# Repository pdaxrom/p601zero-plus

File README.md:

## Pyldin-601 compatible retrocomputer.

[History](docs/HISTORY.md)

### Overview hardware version 2.0:

 Function | Description 
----|----
CPU | [System 11 - VHDL 68HC11](http://members.optusnet.com.au/jekent/system11/)
FPGA| [Lattice MachXO2-4000HC module](http://www.stepfpga.com)
RAM | Builtin FPGA 4KB and/or external static serial ram 2x128KB
ROM | Builtin FPGA BOOTROM 2KB
Keyboard | PS/2
Serial port | 1 serial port and 1 UART (rx/tx only)
Parallel port | 2x8bit
Video | TV (color, 8bit DAC)
Audio | YMZ284-D (mono)
Storage | MMC/SD
Other | Onboard SPI, 4 CS ports and Reset.

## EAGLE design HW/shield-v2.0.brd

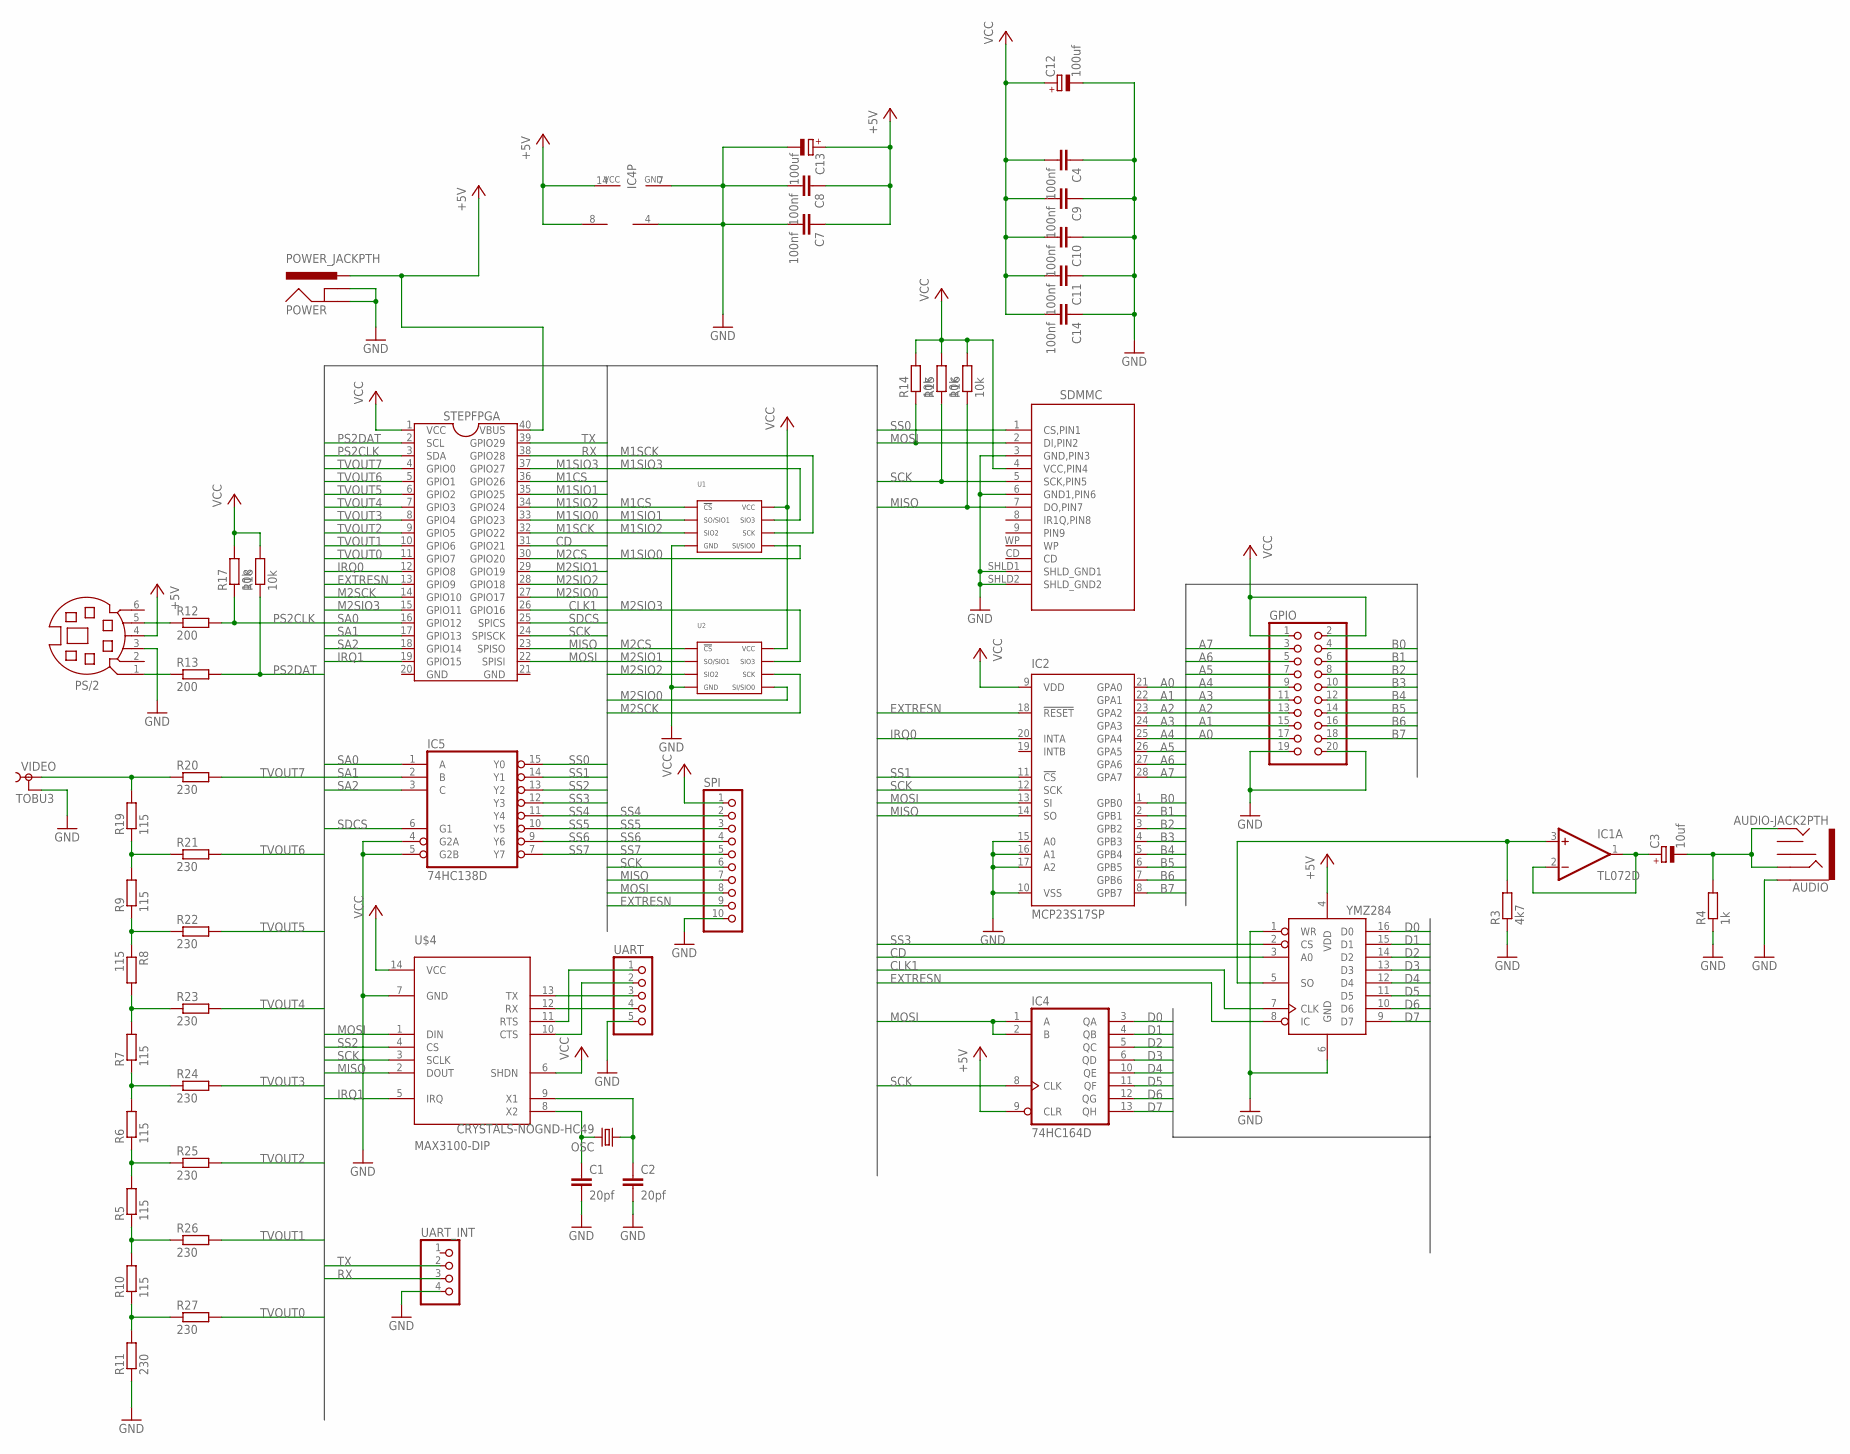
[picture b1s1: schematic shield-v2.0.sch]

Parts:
AUDIO: AUDIO-JACK2PTH; AUDIO-JACK
C1, C2: 20pf; 1206
C3: 10uf; E5-5
C4, C7, C8, C9, C10, C11, C14: 100nf; 1206
C12, C13: 100uf; E5-5
GPIO: PINHD-2X10; 2X10
IC1: TL072D; SO08
IC2: MCP23S17SP; DIL28-3
IC3: YMZ284; DIL16
IC4: 74HC164D; SO14
IC5: 74HC138D; SO16
OSC: CRYSTALS-NOGND-HC49; HC49
POWER: POWER_JACKPTH; POWER_JACK_PTH
PS/2: MD06SS; MDIN06SS
R3: 4k7; R1206
R4: 1k; R1206
R5, R6, R7, R8, R9, R10, R19: 115; R1206
R11, R20, R21, R22, R23, R24, R25, R26, R27: 230; R1206
R12, R13: 200; R1206
R14, R15, R16, R17, R18: 10k; R1206
SDMMC: FCI_SD_SOCKET; SD-MMC_SOCKET-PP
SPI: PINHD-1X10; 1X10
STEPFPGA: STEPFPGA; DIL40
U1, U2: 23A1024/23LC1024-I/SN; 23A1024_SOIC-8
U$4: MAX3100-DIP; DIL14
UART: PINHD-1X5; 1X05
UART_INT: PINHD-1X4; 1X04
VIDEO: TOBU3

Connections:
+5V: C7.1, C8.1, C13.+, IC1.8 (V+), IC3.4 (VDD), IC4.9 (CLR), IC4.14 (VCC), POWER.PWR, PS/2.4, STEPFPGA.40 (VBUS)
A0: GPIO.17, IC2.21 (GPA0)
A1: GPIO.15, IC2.22 (GPA1)
A2: GPIO.13, IC2.23 (GPA2)
A3: GPIO.11, IC2.24 (GPA3)
A4: GPIO.9, IC2.25 (GPA4)
A5: GPIO.7, IC2.26 (GPA5)
A6: GPIO.5, IC2.27 (GPA6)
A7: GPIO.3, IC2.28 (GPA7)
B0: GPIO.4, IC2.1 (GPB0)
B1: GPIO.6, IC2.2 (GPB1)
B2: GPIO.8, IC2.3 (GPB2)
B3: GPIO.10, IC2.4 (GPB3)
B4: GPIO.12, IC2.5 (GPB4)
B5: GPIO.14, IC2.6 (GPB5)
B6: GPIO.16, IC2.7 (GPB6)
B7: GPIO.18, IC2.8 (GPB7)
CD: IC3.3 (A0), STEPFPGA.31 (GPIO21)
CLK1: IC3.7 (CLK), STEPFPGA.26 (GPIO16)
D0: IC3.16 (D0), IC4.3 (QA)
D1: IC3.15 (D1), IC4.4 (QB)
D2: IC3.14 (D2), IC4.5 (QC)
D3: IC3.13 (D3), IC4.6 (QD)
D4: IC3.12 (D4), IC4.10 (QE)
D5: IC3.11 (D5), IC4.11 (QF)
D6: IC3.10 (D6), IC4.12 (QG)
D7: IC3.9 (D7), IC4.13 (QH)
EXTRESN: IC2.18 (!RESET), IC3.8 (IC), SPI.9, STEPFPGA.13 (GPIO9)
GND: AUDIO.SLEEVE, C1.2, C2.2, C4.1, C7.2, C8.2, C9.1, C10.1, C11.1, C12.-, C13.-, C14.1, GPIO.19, GPIO.20, IC1.4 (V-), IC2.10 (VSS), IC2.15 (A0), IC2.16 (A1), IC2.17 (A2), IC3.1 (WR), IC3.6 (GND), IC4.7 (GND), IC5.4 (G2A), IC5.5 (G2B), IC5.8 (GND), POWER.GND, POWER.GNDBREAK, PS/2.3, R3.1, R4.1, R11.1, SDMMC.3 (GND,PIN3), SDMMC.6 (GND1,PIN6), SDMMC.SHLD1 (SHLD_GND1), SDMMC.SHLD2 (SHLD_GND2), SPI.10, STEPFPGA.20 (GND), STEPFPGA.21 (GND), U1.4 (GND), U2.4 (GND), U$4.7 (GND), UART.5, UART_INT.4, VIDEO.2, VIDEO.2@1 (2), VIDEO.2@2 (2)
IRQ0: IC2.20 (INTA), STEPFPGA.12 (GPIO8)
IRQ1: STEPFPGA.19 (GPIO15), U$4.5 (IRQ)
M1CS: STEPFPGA.36 (GPIO26), U1.1 (CS')
M1SCK: STEPFPGA.32 (GPIO22), U1.6 (SCK)
M1SIO0: STEPFPGA.33 (GPIO23), U1.5 (SI/SIO0)
M1SIO1: STEPFPGA.35 (GPIO25), U1.2 (SO/SIO1)
M1SIO2: STEPFPGA.34 (GPIO24), U1.3 (SIO2)
M1SIO3: STEPFPGA.37 (GPIO27), U1.7 (SIO3)
M2CS: STEPFPGA.30 (GPIO20), U2.1 (CS')
M2SCK: STEPFPGA.14 (GPIO10), U2.6 (SCK)
M2SIO0: STEPFPGA.27 (GPIO17), U2.5 (SI/SIO0)
M2SIO1: STEPFPGA.29 (GPIO19), U2.2 (SO/SIO1)
M2SIO2: STEPFPGA.28 (GPIO18), U2.3 (SIO2)
M2SIO3: STEPFPGA.15 (GPIO11), U2.7 (SIO3)
MISO: IC2.14 (SO), R16.1, SDMMC.7 (DO,PIN7), SPI.7, STEPFPGA.23 (SPISO), U$4.2 (DOUT)
MOSI: IC2.13 (SI), IC4.1 (A), IC4.2 (B), R14.1, SDMMC.2 (DI,PIN2), SPI.8, STEPFPGA.22 (SPISI), U$4.1 (DIN)
unnamed: C1.1, OSC.2, U$4.8 (X2)
unnamed: U$4.13 (TX), UART.3
unnamed: U$4.12 (RX), UART.4
unnamed: U$4.11 (RTS), UART.1
unnamed: U$4.10 (CTS), UART.2
unnamed: C2.1, OSC.1, U$4.9 (X1)
unnamed: IC1.3 (+IN), IC3.5 (SO), R3.2
unnamed: C3.+, IC1.1 (OUT), IC1.2 (-IN)
unnamed: R19.2, R20.1, VIDEO.1
unnamed: AUDIO.RING, AUDIO.TIP, C3.-, R4.2
unnamed: R9.2, R19.1, R21.1
unnamed: R8.1, R9.1, R22.1
unnamed: R7.2, R8.2, R23.1
unnamed: R6.2, R7.1, R24.1
unnamed: R5.2, R6.1, R25.1
unnamed: R5.1, R10.2, R26.1
unnamed: R10.1, R11.2, R27.1
unnamed: PS/2.5, R12.1
unnamed: PS/2.1, R13.1
PS2CLK: R12.2, R17.1, STEPFPGA.3 (SDA)
PS2DAT: R13.2, R18.1, STEPFPGA.2 (SCL)
RX: STEPFPGA.38 (GPIO28), UART_INT.3
SA0: IC5.1 (A), STEPFPGA.16 (GPIO12)
SA1: IC5.2 (B), STEPFPGA.17 (GPIO13)
SA2: IC5.3 (C), STEPFPGA.18 (GPIO14)
SCK: IC2.12 (SCK), IC4.8 (CLK), R15.1, SDMMC.5 (SCK,PIN5), SPI.6, STEPFPGA.24 (SPISCK), U$4.3 (SCLK)
SDCS: IC5.6 (G1), STEPFPGA.25 (SPICS)
SS0: IC5.15 (Y0), SDMMC.1 (CS,PIN1)
SS1: IC2.11 (!CS), IC5.14 (Y1)
SS2: IC5.13 (Y2), U$4.4 (CS)
SS3: IC3.2 (CS), IC5.12 (Y3)
SS4: IC5.11 (Y4), SPI.2
SS5: IC5.10 (Y5), SPI.3
SS6: IC5.9 (Y6), SPI.4
SS7: IC5.7 (Y7), SPI.5
TVOUT0: R27.2, STEPFPGA.11 (GPIO7)
TVOUT1: R26.2, STEPFPGA.10 (GPIO6)
TVOUT2: R25.2, STEPFPGA.9 (GPIO5)
TVOUT3: R24.2, STEPFPGA.8 (GPIO4)
TVOUT4: R23.2, STEPFPGA.7 (GPIO3)
TVOUT5: R22.2, STEPFPGA.6 (GPIO2)
TVOUT6: R21.2, STEPFPGA.5 (GPIO1)
TVOUT7: R20.2, STEPFPGA.4 (GPIO0)
TX: STEPFPGA.39 (GPIO29), UART_INT.2
VCC: C4.2, C9.2, C10.2, C11.2, C12.+, C14.2, GPIO.1, GPIO.2, IC2.9 (VDD), IC5.16 (VCC), R14.2, R15.2, R16.2, R17.2, R18.2, SDMMC.4 (VCC,PIN4), SPI.1, STEPFPGA.1 (VCC), U1.8 (VCC), U2.8 (VCC), U$4.6 (SHDN), U$4.14 (VCC)

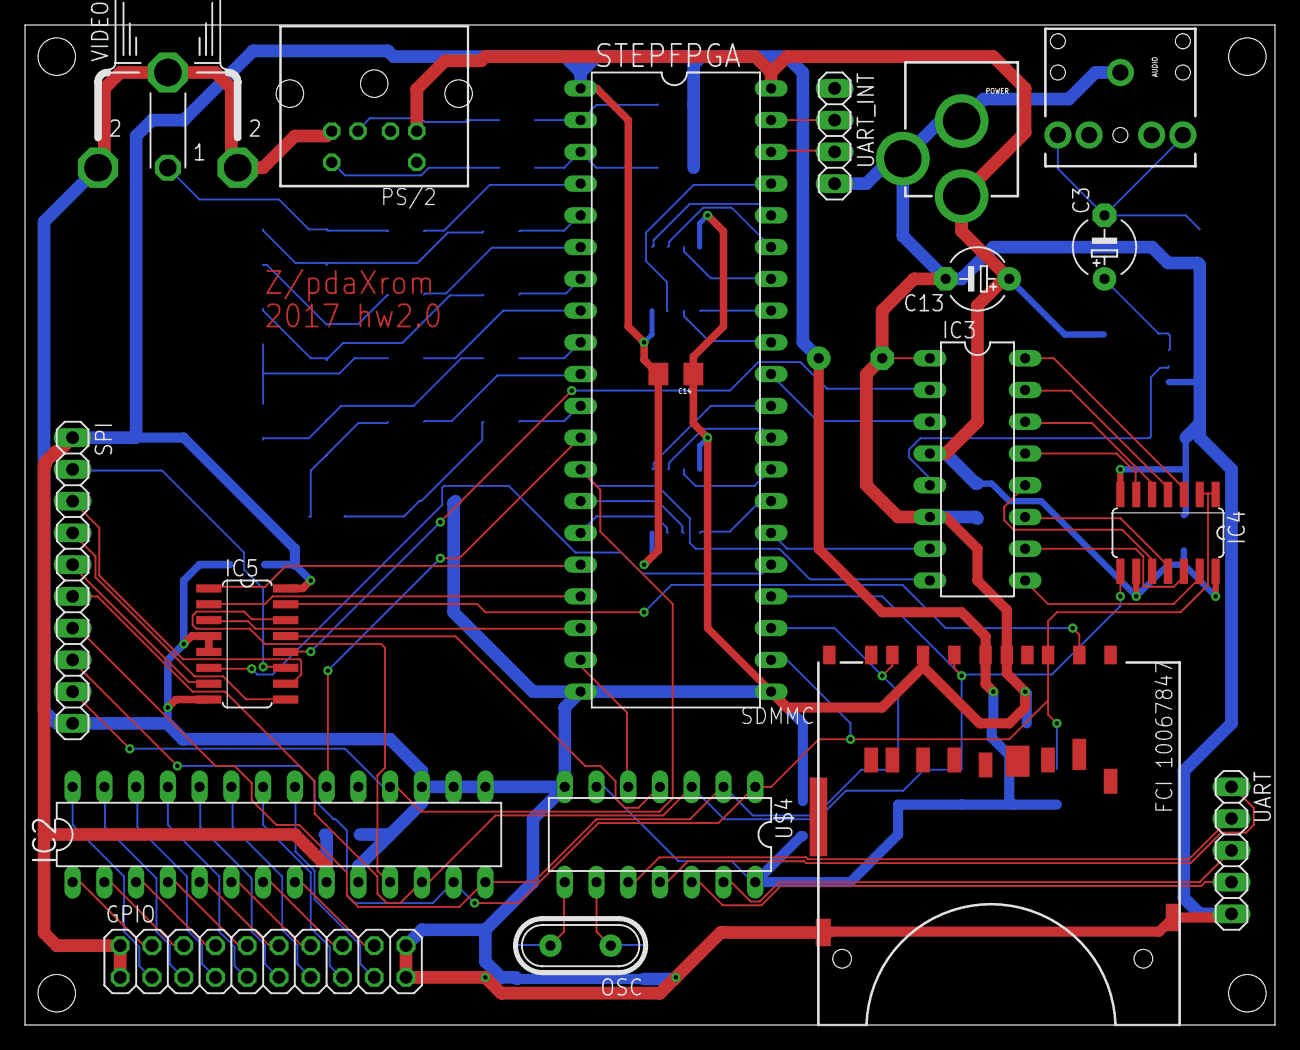
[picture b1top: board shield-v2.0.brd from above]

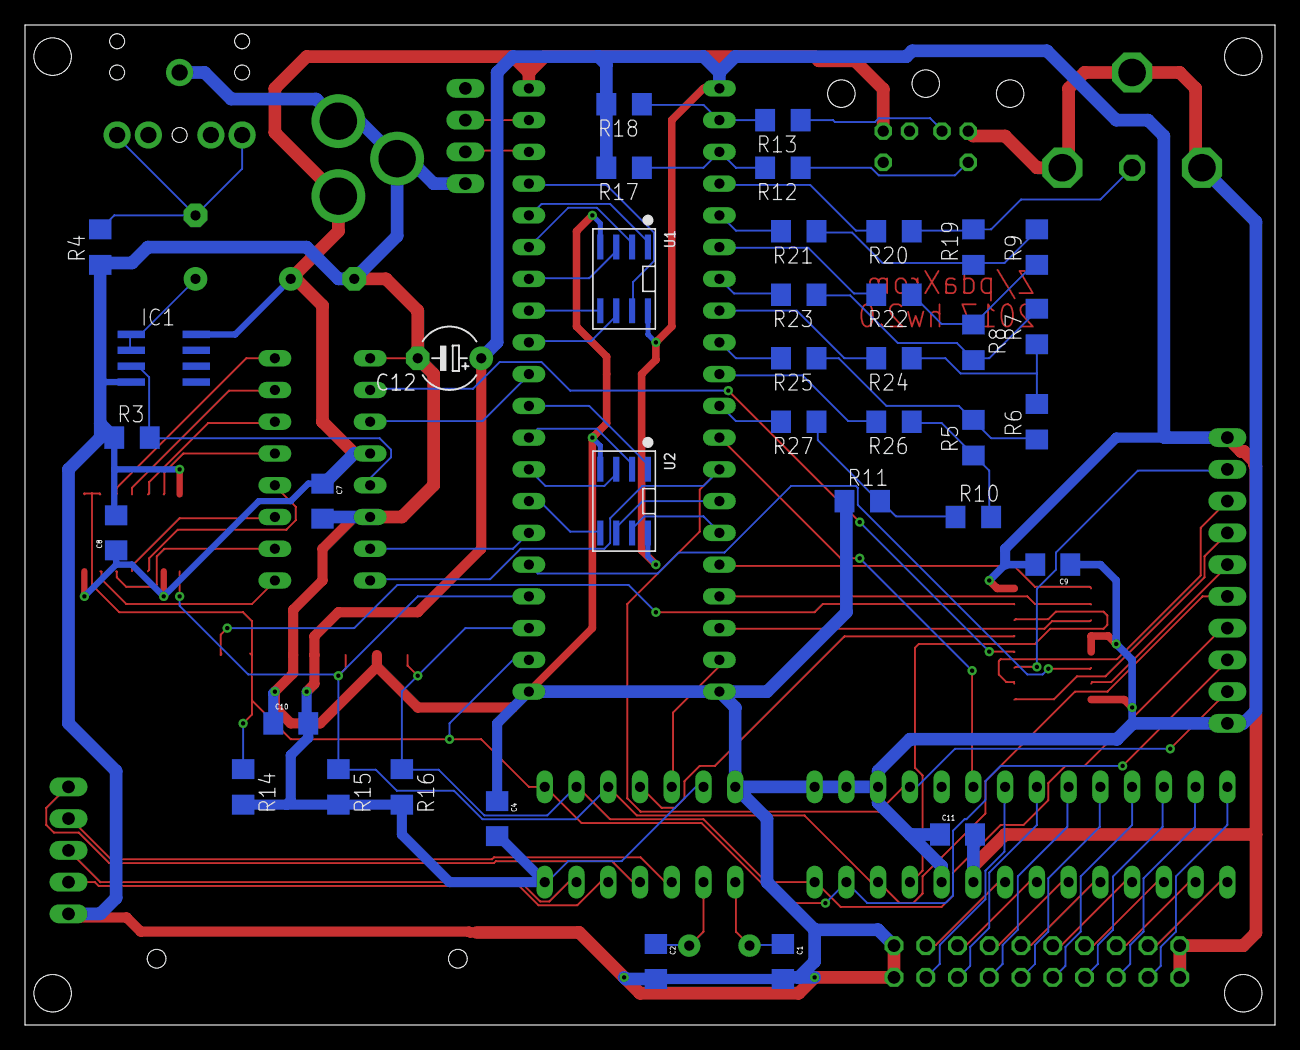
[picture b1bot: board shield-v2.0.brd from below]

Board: 2 copper layers, 100.0 x 80.0 mm, 56 parts (37 on the bottom side), 90 nets.

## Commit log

2017-11-25 Initial, pins layout
2017-12-12 initial hardware version 2.0
2017-12-12 Create README.md
    about
2017-12-12 board photo
2017-12-12 initial (copied from v1)
2017-12-15 initial board support
2017-12-15 remove doubled code
2017-12-15 fixed dma logic with fast cpu

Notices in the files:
parts and their libraries:
SparkFun: Licensing: CC v3.0 Share-Alike You are welcome to use this library for commercial purposes.
